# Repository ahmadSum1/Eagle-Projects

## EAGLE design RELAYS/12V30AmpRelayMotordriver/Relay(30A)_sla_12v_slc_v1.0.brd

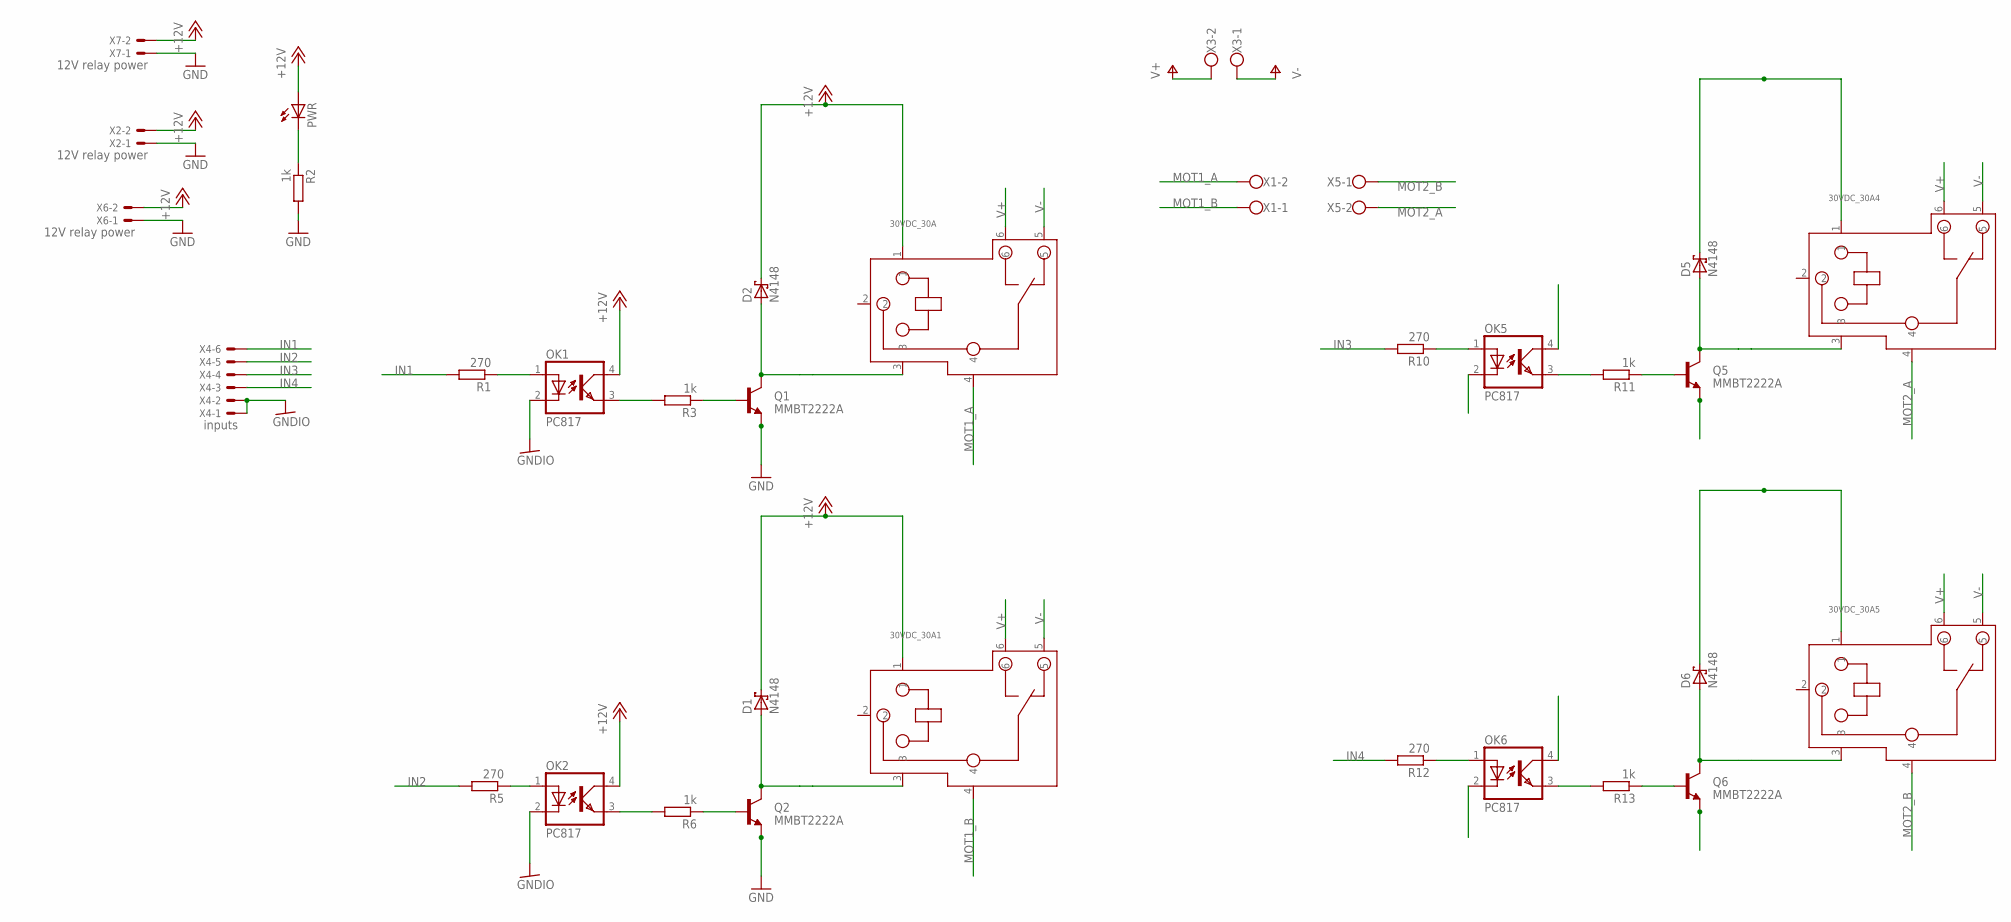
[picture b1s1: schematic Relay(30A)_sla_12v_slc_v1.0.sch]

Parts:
30VDC_30A, 30VDC_30A1, 30VDC_30A4, 30VDC_30A5: RELAY-SLA-05VDC-SL-C; 6P-19.8H
D1, D2, D5, D6: N4148; DIODE_F126Z12
OK1, OK2, OK5, OK6: PC817; DIL04
PWR: LED_ELD260; LED_LD260
Q1, Q2, Q5, Q6: MMBT2222A; TO-92
R1: 270; 0204/7
R2: 1k; 0204/5
R3, R6, R11, R13: 1k; 0204/7
R5, R12: 270; 0204/5
R10: 270; 0207/10
X1, X3, X5: W237-102
X2, X6, X7: 12V relay power; JST-XH-02-PACKAGE-LONG-PAD
X4: inputs; JST-XH-06-PACKAGE-LONG-PAD

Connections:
+12V: 30VDC_30A.1, 30VDC_30A1.1, 30VDC_30A4.1, 30VDC_30A5.1, D1.C (A), D2.C (A), D5.C (A), D6.C (A), OK1.4 (COL), OK2.4 (COL), OK5.4 (COL), OK6.4 (COL), PWR.A, X2.2, X6.2, X7.2
GND: Q1.1 (E), Q2.1 (E), Q5.1 (E), Q6.1 (E), R2.2, X2.1, X6.1, X7.1
GNDIO: OK1.2 (C), OK2.2 (C), OK5.2 (C), OK6.2 (C), X4.1, X4.2
IN1: R1.2, X4.6
IN2: R5.2, X4.5
IN3: R10.2, X4.4
IN4: R12.2, X4.3
MOT1_A: 30VDC_30A.4, X1.2
MOT1_B: 30VDC_30A1.4, X1.1
MOT2_A: 30VDC_30A4.4, X5.2
MOT2_B: 30VDC_30A5.4, X5.1
unnamed: OK1.3 (EMIT), R3.2
unnamed: 30VDC_30A1.3, D1.A (C), Q2.3 (C)
unnamed: PWR.K (C), R2.1
unnamed: OK2.3 (EMIT), R6.2
unnamed: 30VDC_30A.3, D2.A (C), Q1.3 (C)
unnamed: Q1.2 (B), R3.1
unnamed: Q2.2 (B), R6.1
unnamed: OK2.1 (A), R5.1
unnamed: OK1.1 (A), R1.1
unnamed: 30VDC_30A4.3, D5.A (C), Q5.3 (C)
unnamed: 30VDC_30A5.3, D6.A (C), Q6.3 (C)
unnamed: OK6.1 (A), R12.1
unnamed: OK5.1 (A), R10.1
unnamed: OK5.3 (EMIT), R11.2
unnamed: Q5.2 (B), R11.1
unnamed: OK6.3 (EMIT), R13.2
unnamed: Q6.2 (B), R13.1
V+: 30VDC_30A.6, 30VDC_30A1.6, 30VDC_30A4.6, 30VDC_30A5.6, X3.2
V-: 30VDC_30A.5, 30VDC_30A1.5, 30VDC_30A4.5, 30VDC_30A5.5, X3.1

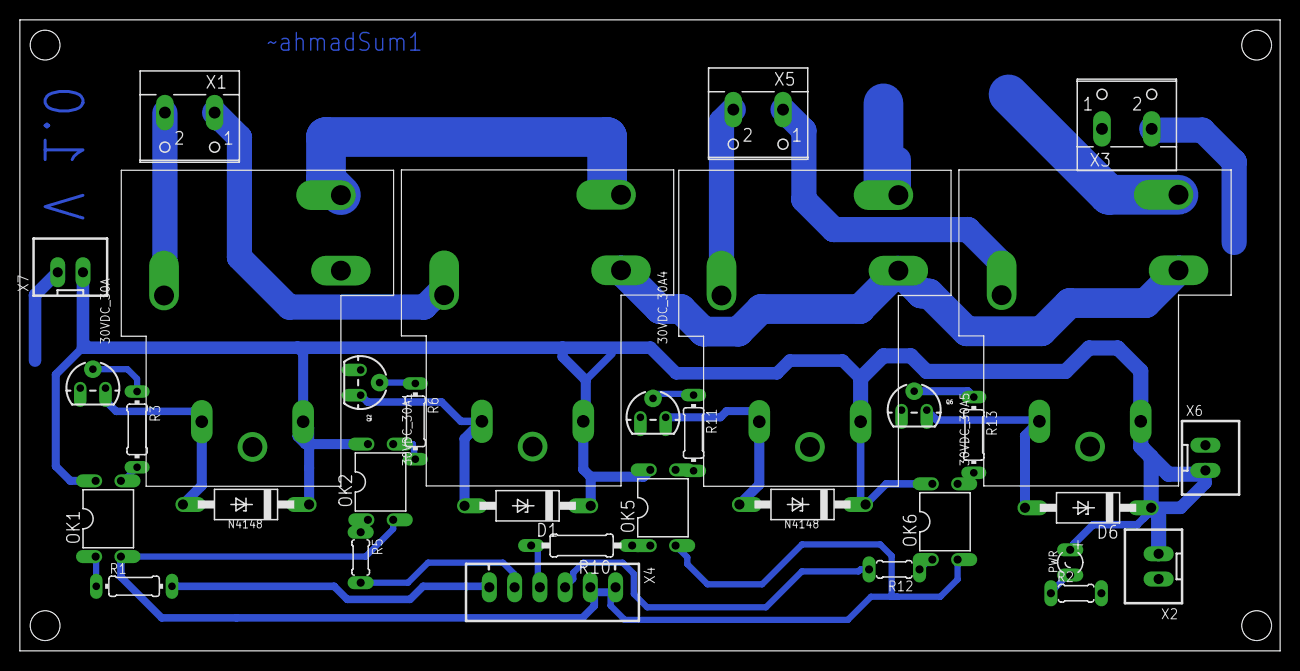
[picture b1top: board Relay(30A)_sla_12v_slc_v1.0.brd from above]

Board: 2 copper layers, 126.8 x 63.5 mm, 33 parts (0 on the bottom side), 30 nets.

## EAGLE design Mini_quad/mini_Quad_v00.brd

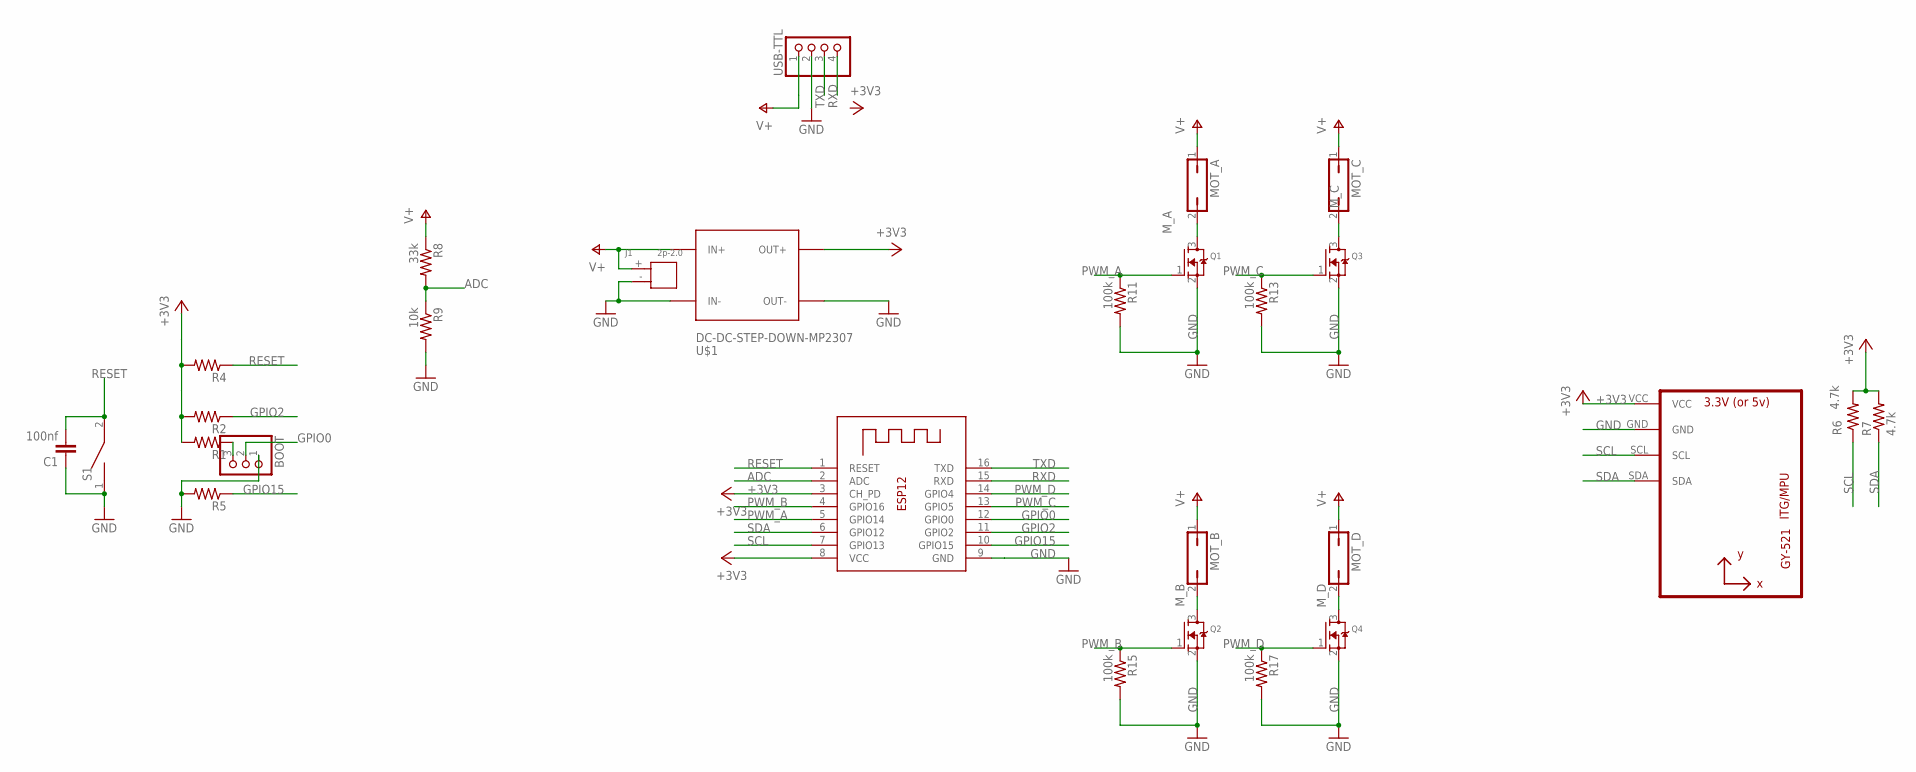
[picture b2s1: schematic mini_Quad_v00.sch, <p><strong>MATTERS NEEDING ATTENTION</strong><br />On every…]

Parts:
BOOT: PINHD-1X3; 1X03
C1: 100nf; C050-024X044
J1: 2p-2.0; H2-2.0-6X4.5MM
MOT_A: JP1Q; JP1
MOT_B: JP1Q; JP1
MOT_C: JP1Q; JP1
MOT_D: JP1Q; JP1
Q1, Q2, Q3, Q4: MOSFET-NTO252; TO252
R1, R2, R5: R-US_0204/5; 0204/5
R4: R-US_0204/7; 0204/7
R6: 4.7k; 0204/5
R7: 4.7k; 0204/7
R8: 33k; 0207/10
R9: 10k; 0204/7
R11, R13, R15, R17: 100k; 0204/5
S1: DS01; DS-01
U1: GY-521MPU6050; GY-521
U$1: DC-DC-STEP-DOWN-MP2307
USB-TTL: PINHD-1X4; 1X04
X1: ESP-12

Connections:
+3V3: R1.2, R2.2, R4.2, R6.2, R7.2, U1.VCC, U$1.OUT+, X1.3 (CH_PD), X1.8 (VCC)
ADC: R8.2, R9.1, X1.2 (ADC)
GND: BOOT.1, C1.1, J1.-, Q1.2 (S), Q2.2 (S), Q3.2 (S), Q4.2 (S), R5.2, R9.2, R11.2, R13.2, R15.2, R17.2, S1.1, U1.GND, U$1.IN-, U$1.OUT-, USB-TTL.2, X1.9 (GND)
GPIO0: BOOT.2, X1.12 (GPIO0)
GPIO2: R2.1, X1.11 (GPIO2)
GPIO15: R5.1, X1.10 (GPIO15)
M_A: MOT_A.2, Q1.3 (D)
M_B: MOT_B.2, Q2.3 (D)
M_C: MOT_C.2, Q3.3 (D)
M_D: MOT_D.2, Q4.3 (D)
unnamed: BOOT.3, R1.1
PWM_A: Q1.1 (G), R11.1, X1.5 (GPIO14)
PWM_B: Q2.1 (G), R15.1, X1.4 (GPIO16)
PWM_C: Q3.1 (G), R13.1, X1.13 (GPIO5)
PWM_D: Q4.1 (G), R17.1, X1.14 (GPIO4)
RESET: C1.2, R4.1, S1.2, X1.1 (RESET)
RXD: USB-TTL.4, X1.15 (RXD)
SCL: R6.1, U1.SCL, X1.7 (GPIO13)
SDA: R7.1, U1.SDA, X1.6 (GPIO12)
TXD: USB-TTL.3, X1.16 (TXD)
V+: J1.+, MOT_A.1, MOT_B.1, MOT_C.1, MOT_D.1, R8.1, U$1.IN+, USB-TTL.1

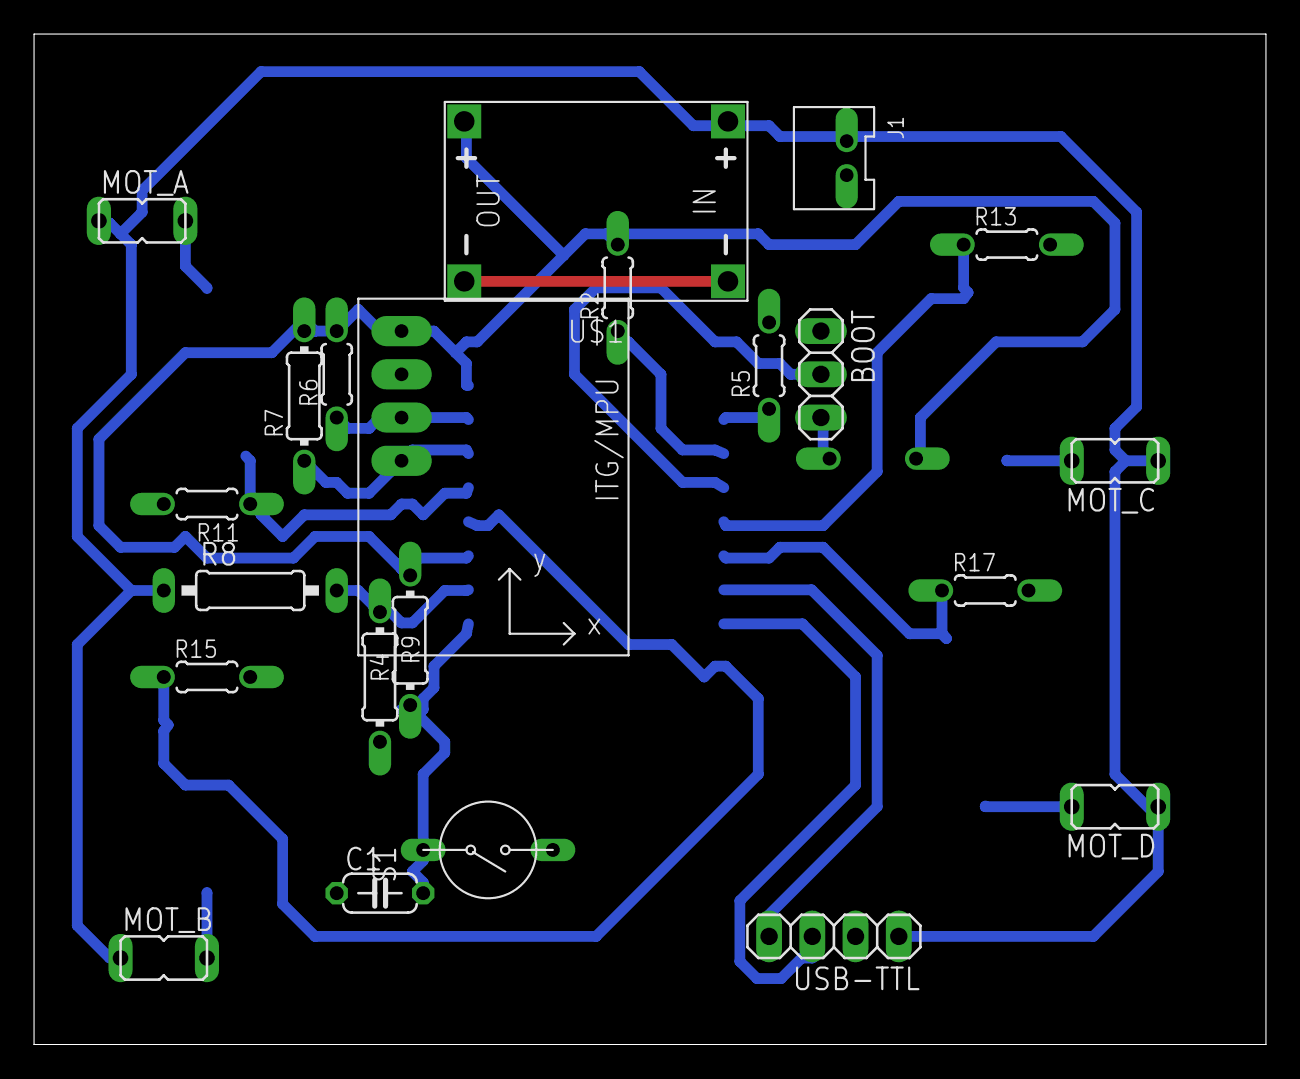
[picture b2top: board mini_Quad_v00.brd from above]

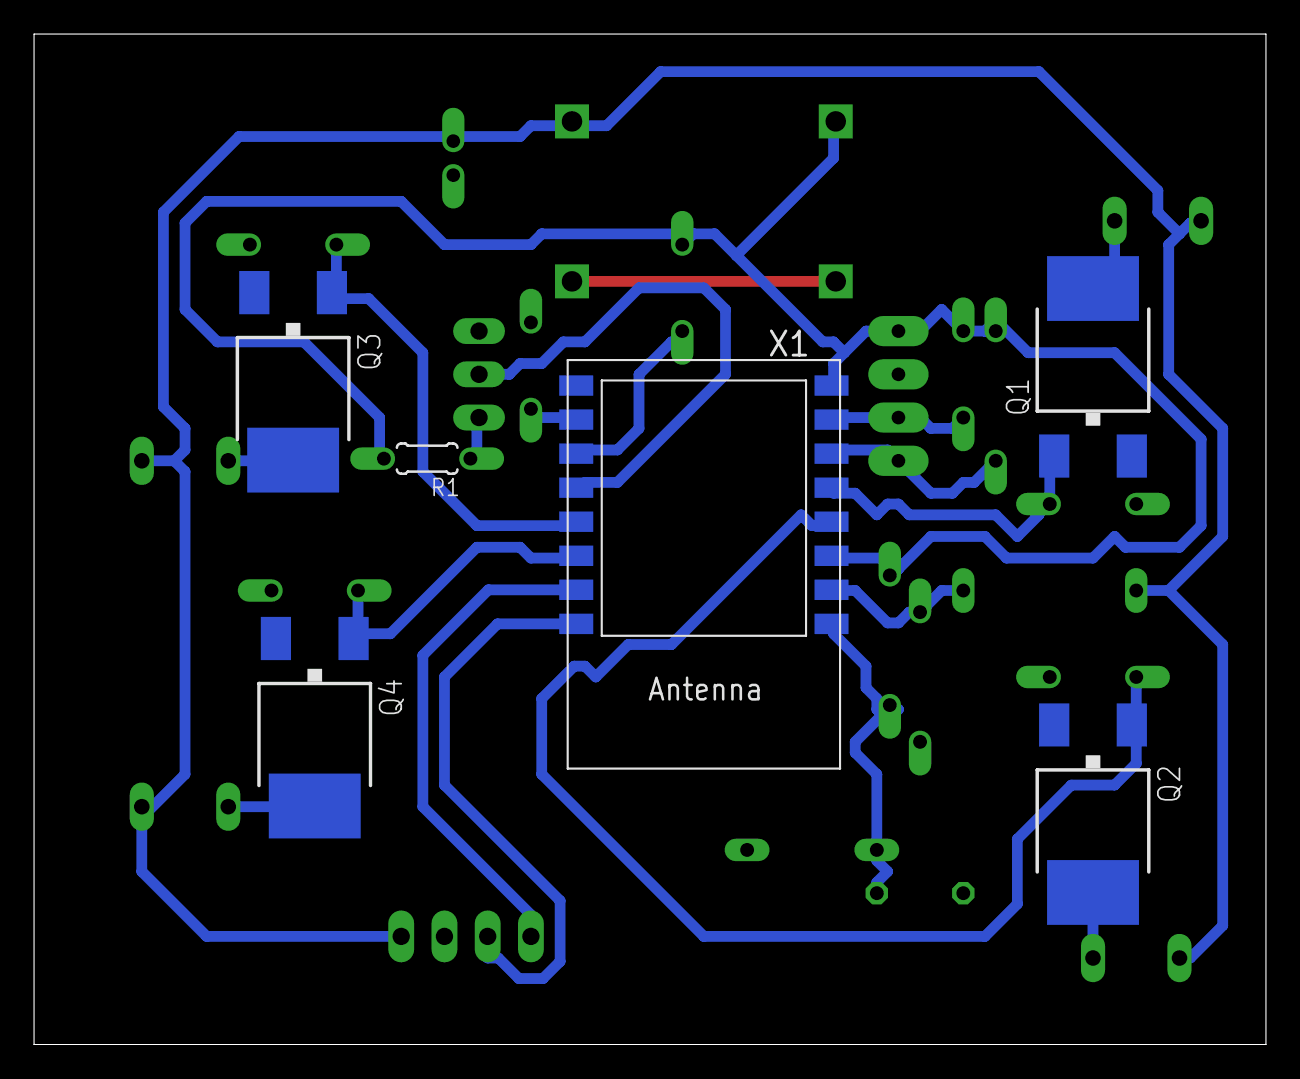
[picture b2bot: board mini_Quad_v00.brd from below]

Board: 2 copper layers, 72.4 x 59.4 mm, 28 parts (6 on the bottom side), 21 nets.

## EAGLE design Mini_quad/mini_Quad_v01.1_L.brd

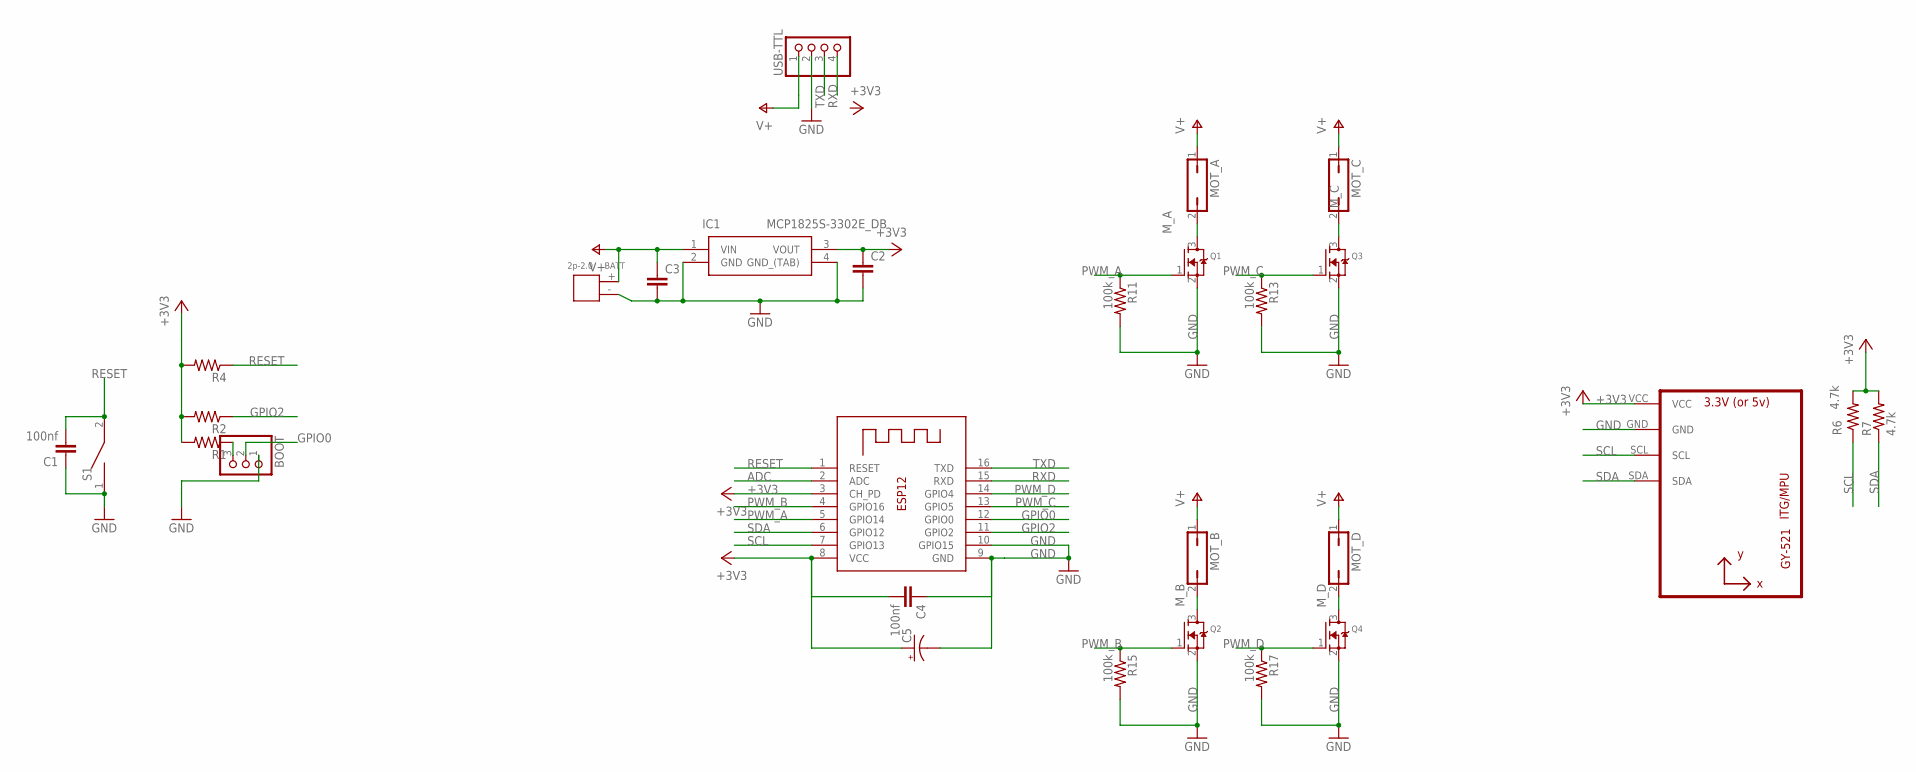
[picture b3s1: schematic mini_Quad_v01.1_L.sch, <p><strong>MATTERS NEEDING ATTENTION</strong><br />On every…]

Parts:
BATT: 2p-2.0; H2-2.0-6X4.5MM
BOOT: PINHD-1X3; 1X03
C1: 100nf; C1206K
C2, C3: C-EUC1206K; C1206K
C4: 100nf; C050-024X044
C5: CPOL-USB/3528-21W; B/3528-21W
ESP12-E: ESP-12
IC1: MCP1825S-3302E_DB; SOT230P700X180-4N
MOT_A: JP1Q; JP1
MOT_B: JP1Q; JP1
MOT_C: JP1Q; JP1
MOT_D: JP1Q; JP1
Q1, Q2, Q3, Q4: MOSFET-NTO252; TO252
R1: R-US_R1206W; R1206W
R2: R-US_0204/5; 0204/5
R4: R-US_0204/7; 0204/7
R6: 4.7k; 0204/5
R7: 4.7k; 0204/7
R11, R13, R15, R17: 100k; 0204/5
S1: DS01; DS-01
U1: GY-521MPU6050; GY-521
USB-TTL: PINHD-1X4; 1X04

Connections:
+3V3: C2.1, C4.2, C5.+, ESP12-E.3 (CH_PD), ESP12-E.8 (VCC), IC1.3 (VOUT), R1.2, R2.2, R4.2, R6.2, R7.2, U1.VCC
ADC: ESP12-E.2 (ADC)
GND: BATT.-, BOOT.1, C1.1, C2.2, C3.2, C4.1, C5.-, ESP12-E.9 (GND), ESP12-E.10 (GPIO15), IC1.2 (GND), IC1.4 (GND_(TAB)), Q1.2 (S), Q2.2 (S), Q3.2 (S), Q4.2 (S), R11.2, R13.2, R15.2, R17.2, S1.1, U1.GND, USB-TTL.2
GPIO0: BOOT.2, ESP12-E.12 (GPIO0)
GPIO2: ESP12-E.11 (GPIO2), R2.1
M_A: MOT_A.2, Q1.3 (D)
M_B: MOT_B.2, Q2.3 (D)
M_C: MOT_C.2, Q3.3 (D)
M_D: MOT_D.2, Q4.3 (D)
unnamed: BOOT.3, R1.1
PWM_A: ESP12-E.5 (GPIO14), Q1.1 (G), R11.1
PWM_B: ESP12-E.4 (GPIO16), Q2.1 (G), R15.1
PWM_C: ESP12-E.13 (GPIO5), Q3.1 (G), R13.1
PWM_D: ESP12-E.14 (GPIO4), Q4.1 (G), R17.1
RESET: C1.2, ESP12-E.1 (RESET), R4.1, S1.2
RXD: ESP12-E.15 (RXD), USB-TTL.4
SCL: ESP12-E.7 (GPIO13), R6.1, U1.SCL
SDA: ESP12-E.6 (GPIO12), R7.1, U1.SDA
TXD: ESP12-E.16 (TXD), USB-TTL.3
V+: BATT.+, C3.1, IC1.1 (VIN), MOT_A.1, MOT_B.1, MOT_C.1, MOT_D.1, USB-TTL.1

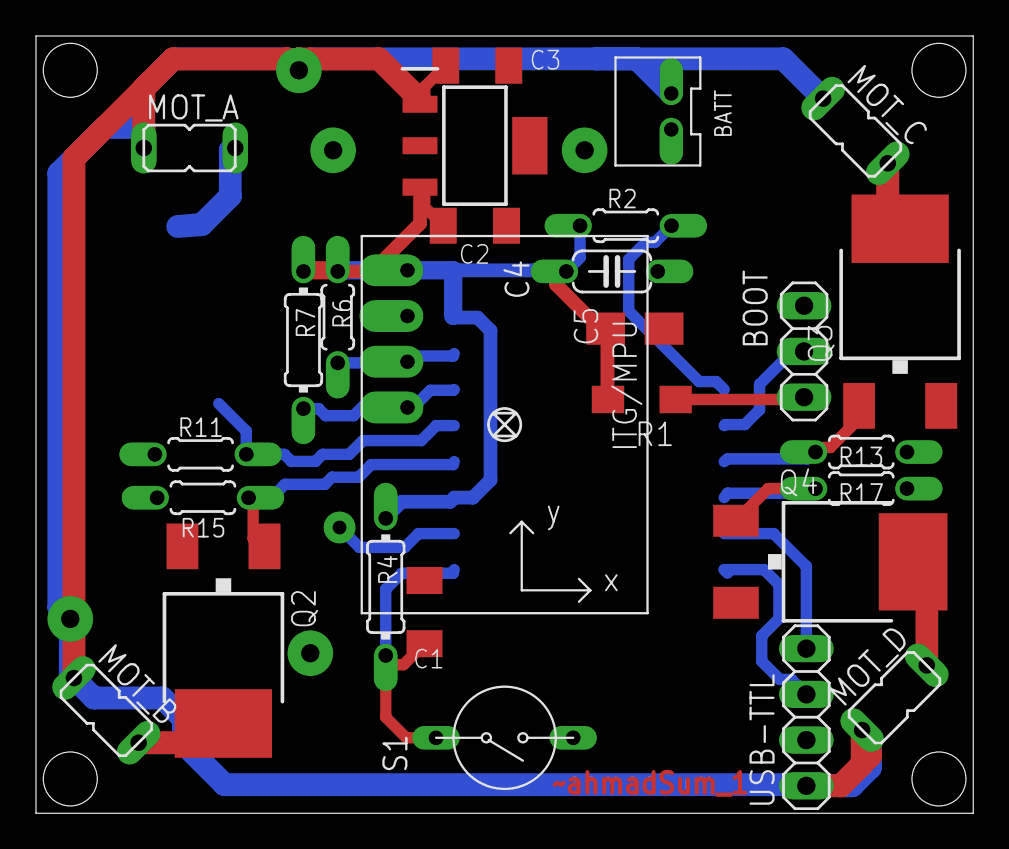
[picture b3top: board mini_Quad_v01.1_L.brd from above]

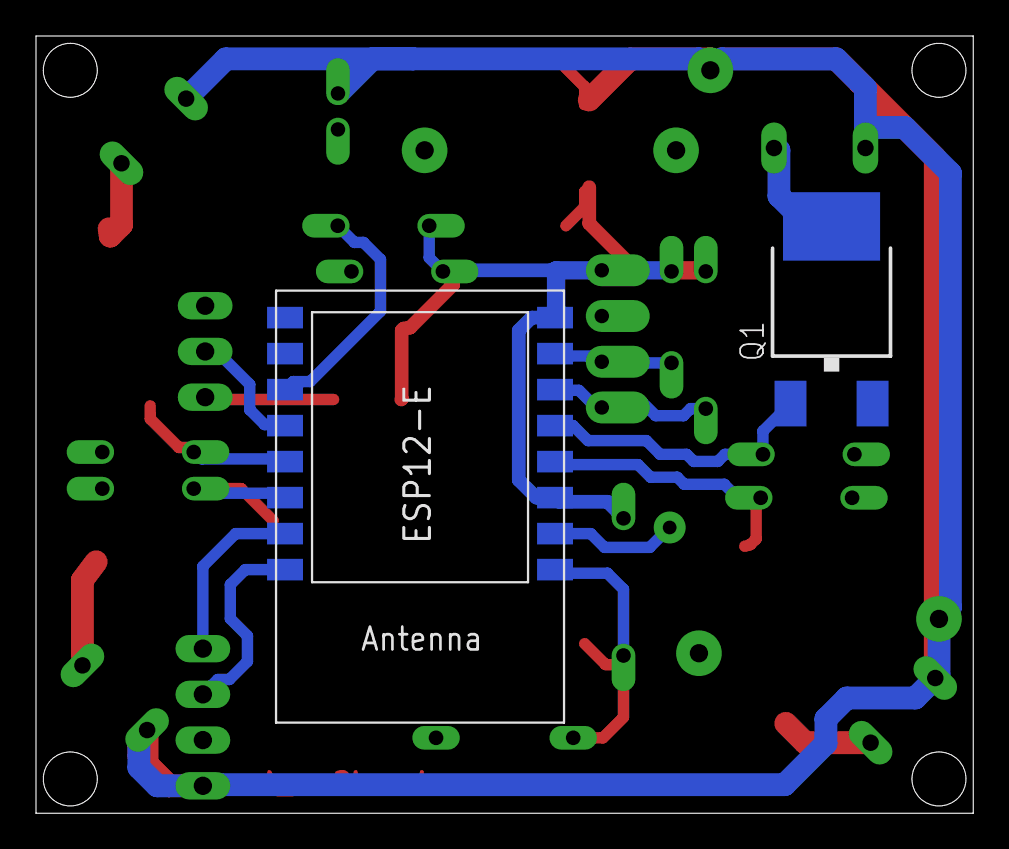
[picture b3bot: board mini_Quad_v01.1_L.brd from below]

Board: 2 copper layers, 52.1 x 43.2 mm, 29 parts (2 on the bottom side), 19 nets.
